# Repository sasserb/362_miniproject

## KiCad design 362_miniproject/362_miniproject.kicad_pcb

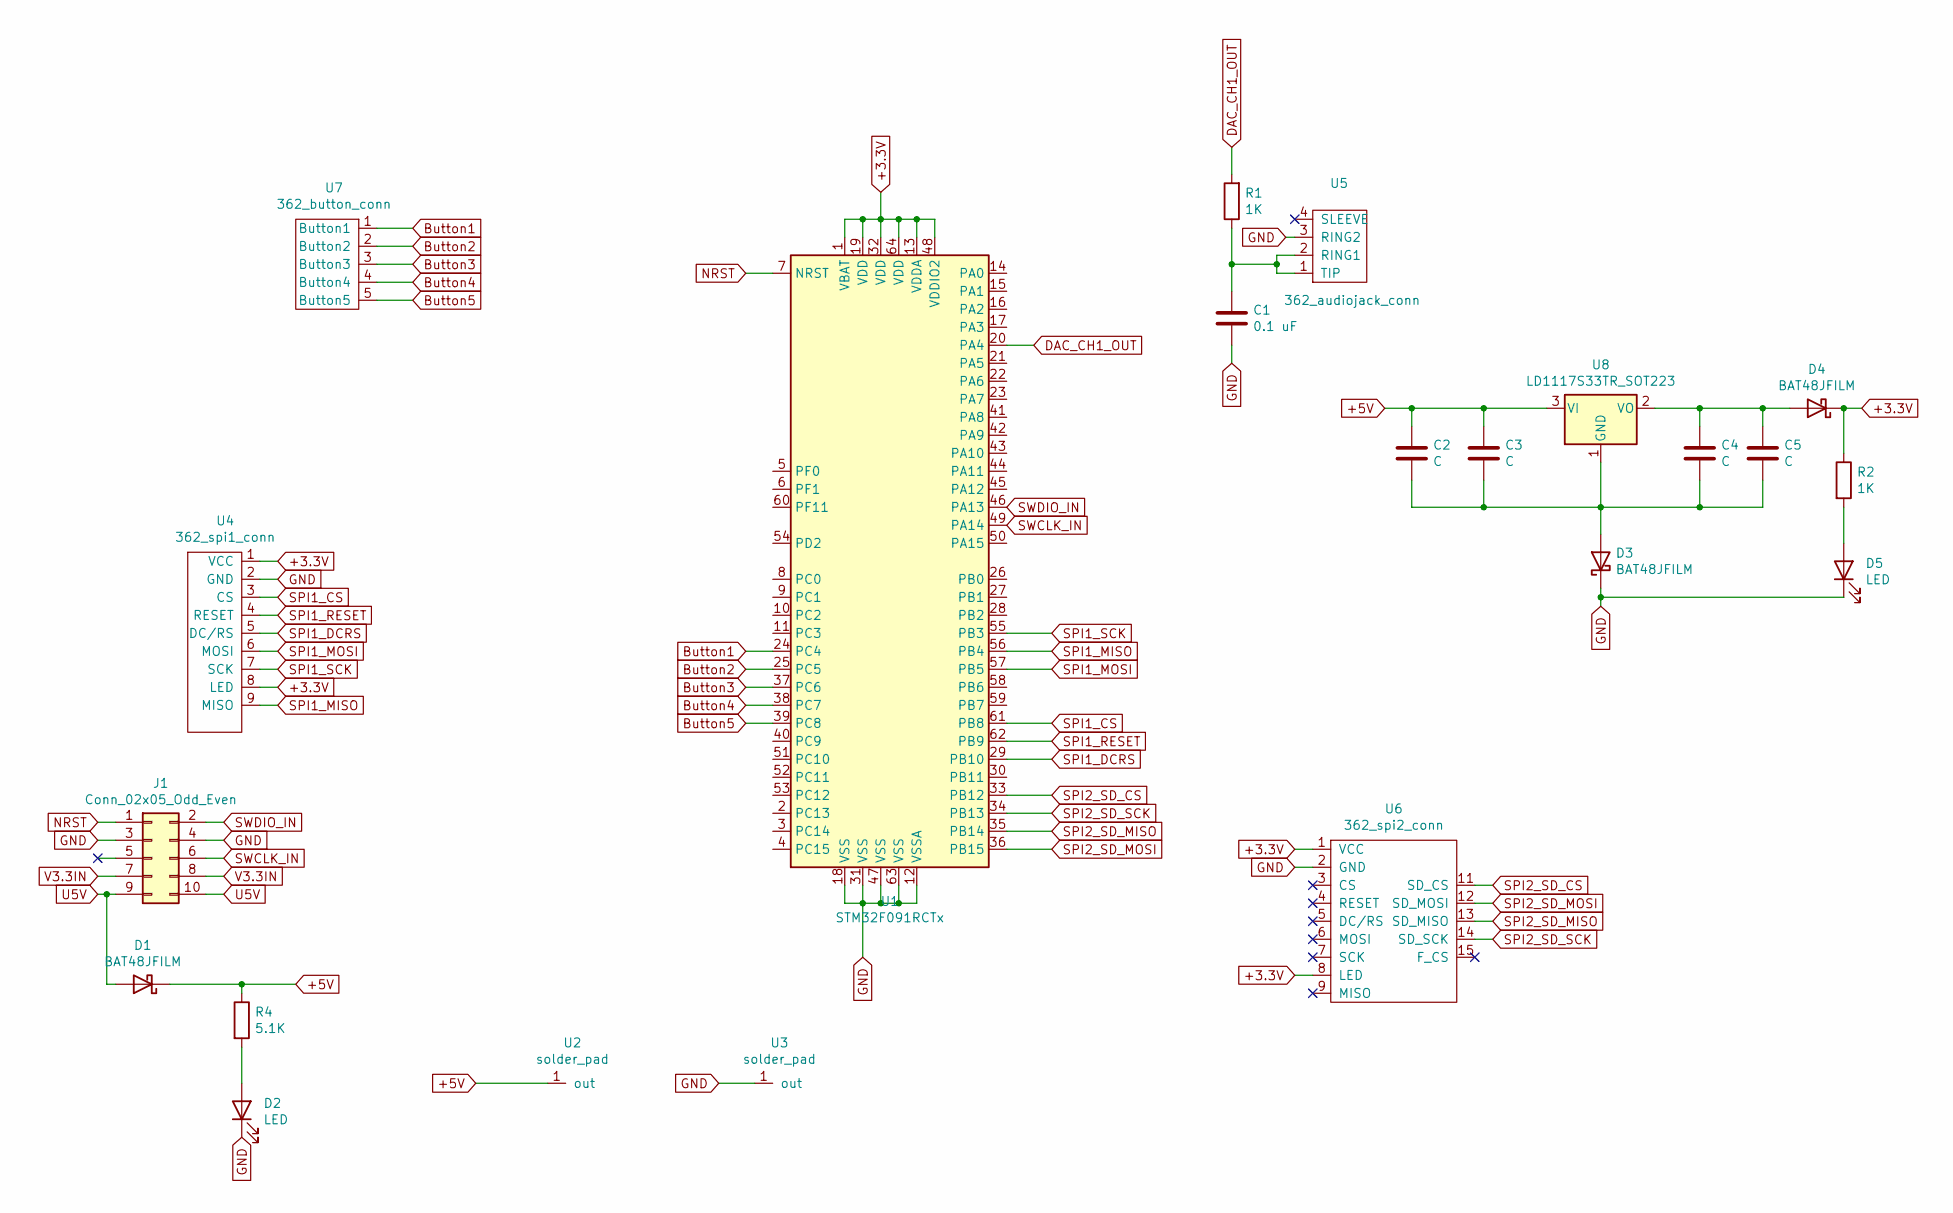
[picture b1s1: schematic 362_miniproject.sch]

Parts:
C1: 0.1 uF; C_0805_2012Metric_Pad1.18x1.45mm_HandSolder
C2, C3, C4, C5: C; C_0805_2012Metric_Pad1.18x1.45mm_HandSolder
D1, D3, D4: BAT48JFILM; D_SOD-323
D2, D5: LED; LED_0805_2012Metric
J1: Conn_02x05_Odd_Even; IDC-Header_2x05_P2.54mm_Vertical
R1, R2: 1K; R_0805_2012Metric_Pad1.20x1.40mm_HandSolder
R4: 5.1K; R_0805_2012Metric_Pad1.20x1.40mm_HandSolder
U1: STM32F091RCTx; LQFP-64_10x10mm_P0.5mm
U2, U3: solder_pad; SolderWirePad_1x01_SMD_5x10mm
U4: 362_spi1_conn
U5: 362_audiojack_conn
U6: 362_spi2_conn
U7: 362_button_conn
U8: LD1117S33TR_SOT223; SOT-223-3_TabPin2

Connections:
+3.3V: D4.1 (K), R2.1, U1.1 (VBAT), U1.13 (VDDA), U1.19 (VDD), U1.32 (VDD), U1.48 (VDDIO2), U1.64 (VDD), U4.1 (VCC), U4.8 (LED), U6.1 (VCC), U6.8 (LED)
+5V: C2.1, C3.1, D1.1 (K), R4.1, U2.1, U8.3 (VI)
Button1: U1.24 (PC4), U7.1 (Button1)
Button2: U1.25 (PC5), U7.2 (Button2)
Button3: U1.37 (PC6), U7.3 (Button3)
Button4: U1.38 (PC7), U7.4 (Button4)
Button5: U1.39 (PC8), U7.5 (Button5)
DAC_CH1_OUT: R1.2, U1.20 (PA4)
GND: C1.2, D2.1 (K), D3.1 (K), D5.1 (K), J1.3, J1.4, U1.12 (VSSA), U1.18 (VSS), U1.31 (VSS), U1.47 (VSS), U1.63 (VSS), U3.1, U4.2 (GND), U5.3 (RING2), U6.2 (GND)
NRST: J1.1, U1.7 (NRST)
unnamed: C1.1, R1.1, U5.1 (TIP), U5.2 (RING1)
unnamed: C2.2, C3.2, C4.2, C5.2, D3.2 (A), U8.1 (GND)
unnamed: C4.1, C5.1, D4.2 (A), U8.2 (VO)
unnamed: D2.2 (A), R4.2
unnamed: D5.2 (A), R2.2
SPI1_CS: U1.61 (PB8), U4.3 (CS)
SPI1_DCRS: U1.29 (PB10), U4.5 (DC/RS)
SPI1_MISO: U1.56 (PB4), U4.9 (MISO)
SPI1_MOSI: U1.57 (PB5), U4.6 (MOSI)
SPI1_RESET: U1.62 (PB9), U4.4 (RESET)
SPI1_SCK: U1.55 (PB3), U4.7 (SCK)
SPI2_SD_CS: U1.33 (PB12), U6.11 (SD_CS)
SPI2_SD_MISO: U1.35 (PB14), U6.13 (SD_MISO)
SPI2_SD_MOSI: U1.36 (PB15), U6.12 (SD_MOSI)
SPI2_SD_SCK: U1.34 (PB13), U6.14 (SD_SCK)
SWCLK_IN: J1.6, U1.49 (PA14)
SWDIO_IN: J1.2, U1.46 (PA13)
U5V: D1.2 (A), J1.9, J1.10
V3.3IN: J1.7, J1.8

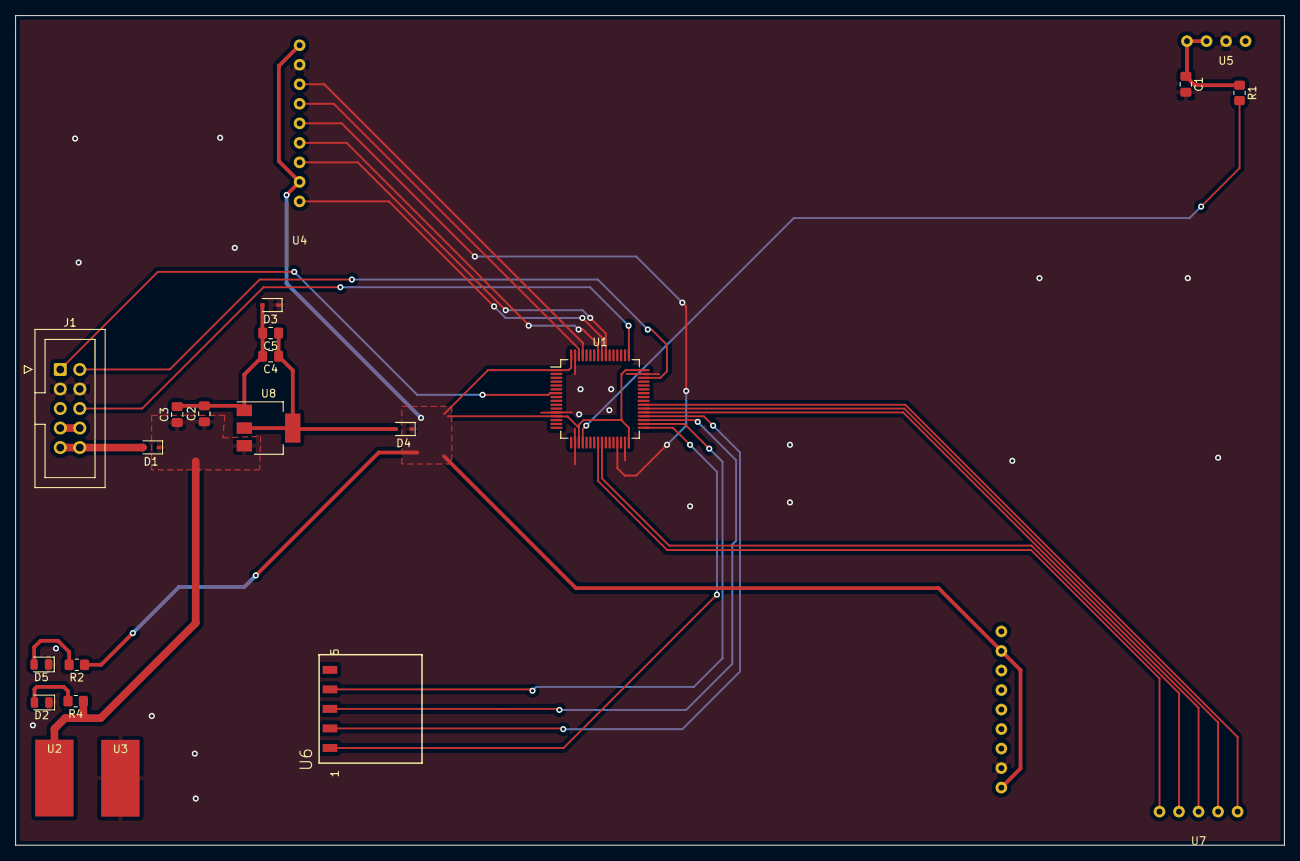
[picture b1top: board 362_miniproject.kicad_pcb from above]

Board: 2 copper layers, 165.1 x 107.9 mm, 22 parts (0 on the bottom side), 29 nets.
